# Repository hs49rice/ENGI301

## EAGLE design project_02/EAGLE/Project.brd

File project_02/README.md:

This directory contains all files for project 2 of ENGI301. The purpose of this project was to design a PCB board in EAGLE for the Clap-On LED Light Strip project.

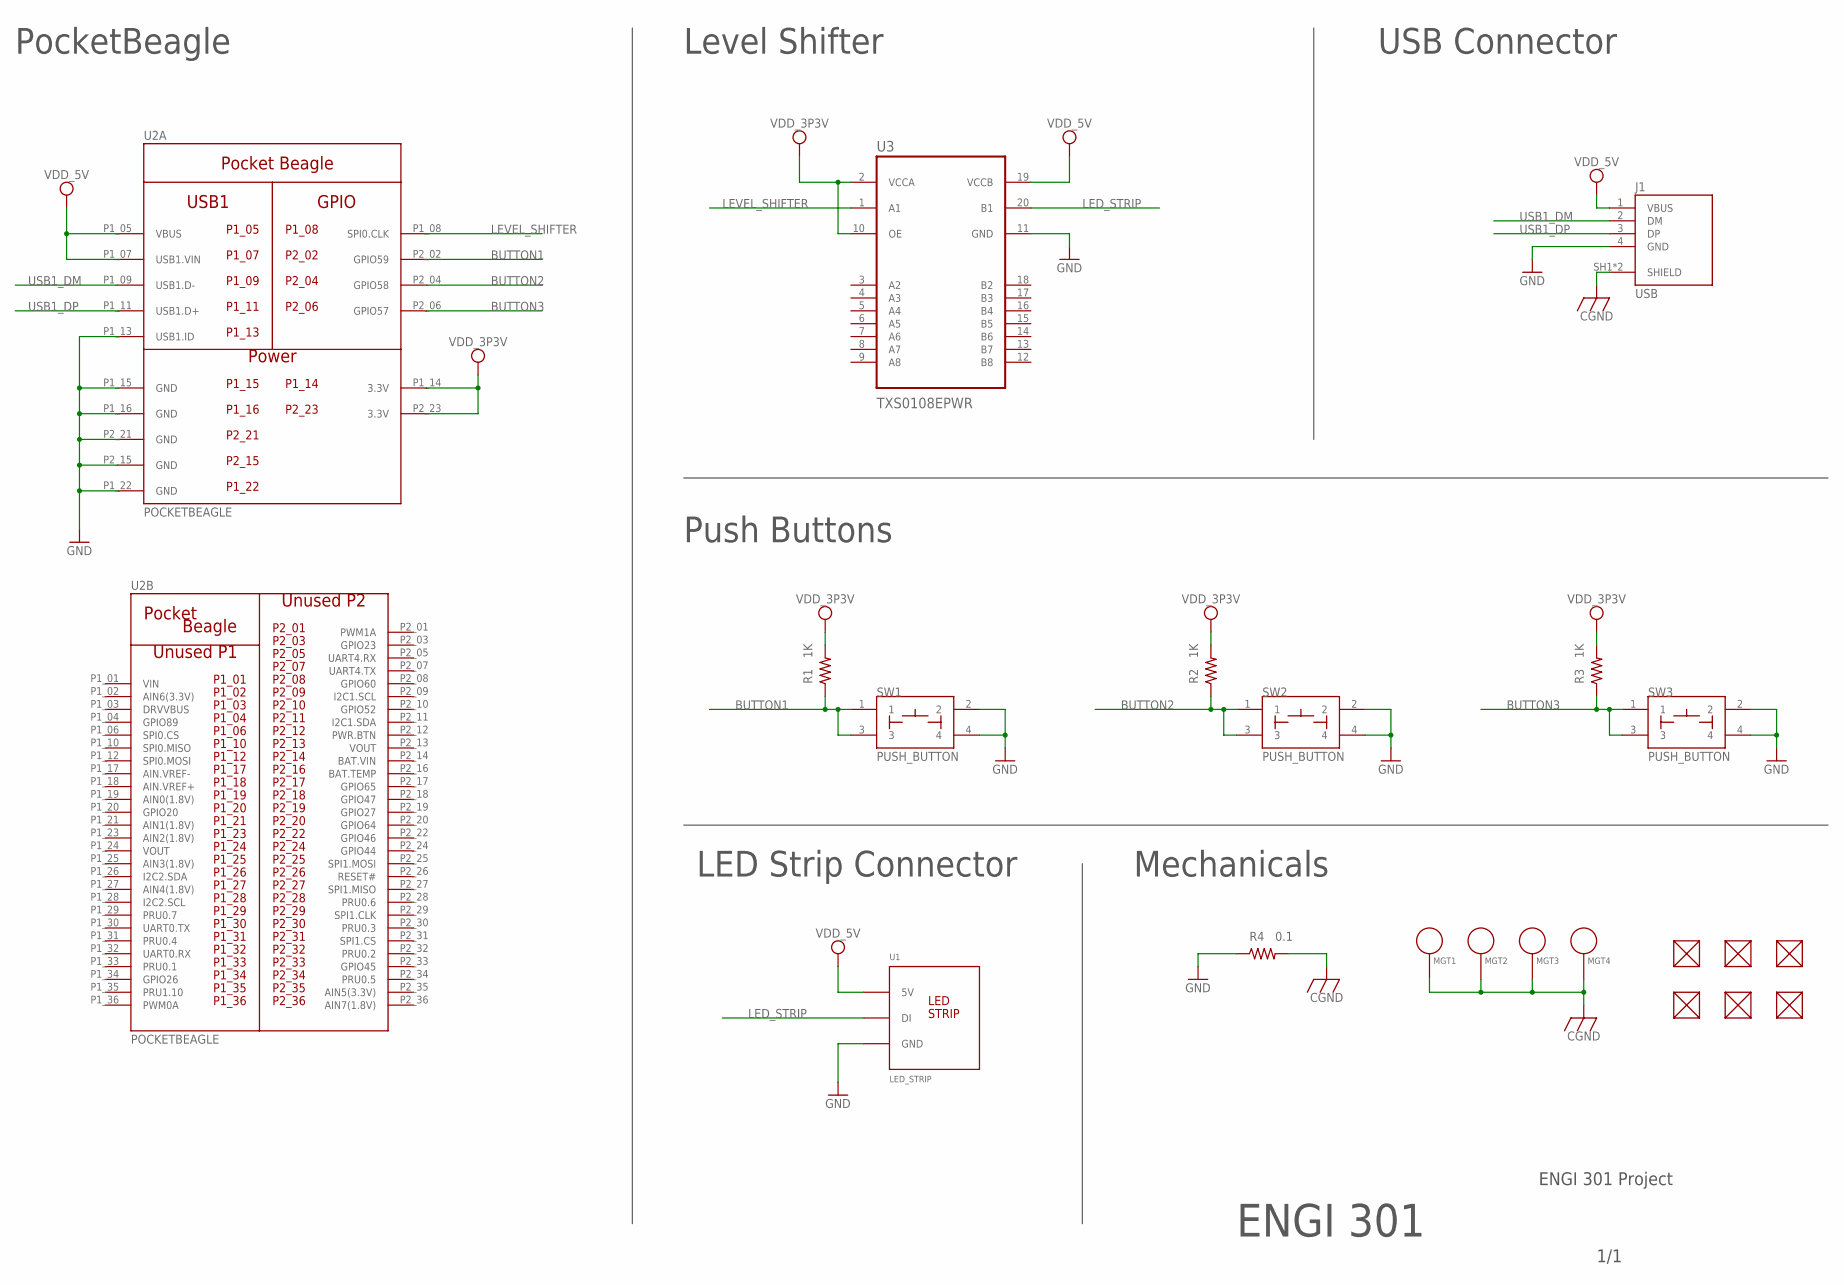
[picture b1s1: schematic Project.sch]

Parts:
FUD1, FUD2, FUD3, FUD4, FUD5, FUD6: FIDUCIAL; FIDUCIAL_40MIL
J1: USB
MGT1, MGT2, MGT3, MGT4: MOUNTING_HOLE
R1, R2, R3: 1K; R0603
R4: 0.1; R0805
SW1, SW2, SW3: PUSH_BUTTON; BUTTON_12.5MM
U1: LED_STRIP
U2: POCKETBEAGLE
U3: TXS0108EPWR; SOP65P640X120-20N

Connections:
BAT.VIN: U2.P2_14 (BAT.VIN)
BUTTON1: R1.1, SW1.1, SW1.3, U2.P2_02 (GPIO59)
BUTTON2: R2.1, SW2.1, SW2.3, U2.P2_04 (GPIO58)
BUTTON3: R3.1, SW3.1, SW3.3, U2.P2_06 (GPIO57)
CGND: J1.SH1 (SHIELD), J1.SH2 (SHIELD), MGT1.P$1, MGT2.P$1, MGT3.P$1, MGT4.P$1, R4.2
GND: J1.4 (GND), R4.1, SW1.2, SW1.4, SW2.2, SW2.4, SW3.2, SW3.4, U1.GND, U2.P1_13 (USB1.ID), U2.P1_15 (GND), U2.P1_16 (GND), U2.P1_22 (GND), U2.P2_15 (GND), U2.P2_21 (GND), U3.11 (GND)
LED_STRIP: U1.SIG (DI), U3.20 (B1)
LEVEL_SHIFTER: U2.P1_08 (SPI0.CLK), U3.1 (A1)
USB1_DM: J1.2 (DM), U2.P1_09 (USB1.D-)
USB1_DP: J1.3 (DP), U2.P1_11 (USB1.D+)
VDD_3P3V: R1.2, R2.2, R3.2, U2.P1_14 (3.3V), U2.P2_23 (3.3V), U3.2 (VCCA), U3.10 (OE)
VDD_5V: J1.1 (VBUS), U1.PWR (5V), U2.P1_05 (VBUS), U2.P1_07 (USB1.VIN), U3.19 (VCCB)
VIN: U2.P1_01 (VIN)
VOUT: U2.P1_24 (VOUT), U2.P2_13 (VOUT)

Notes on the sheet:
ENGI 301 Project
ENGI 301
1/1
PocketBeagle
Level Shifter
USB Connector
Push Buttons
LED Strip Connector
Mechanicals

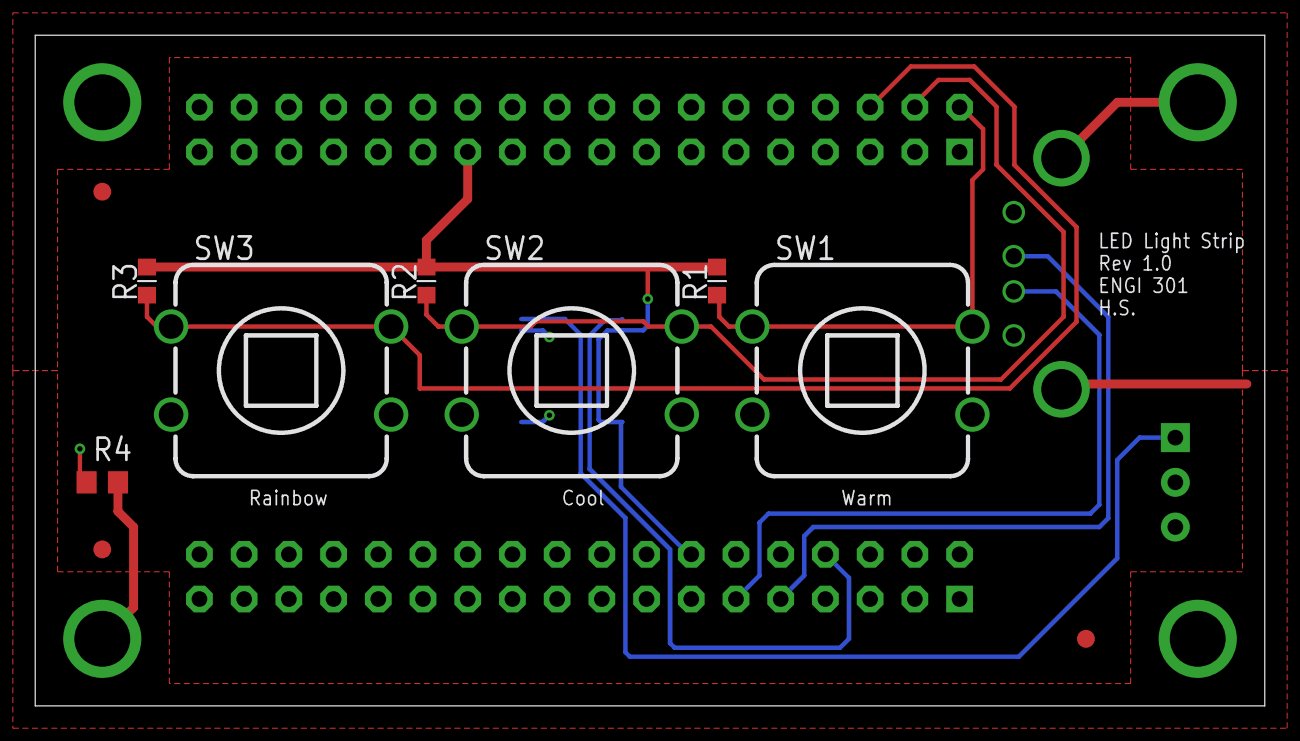
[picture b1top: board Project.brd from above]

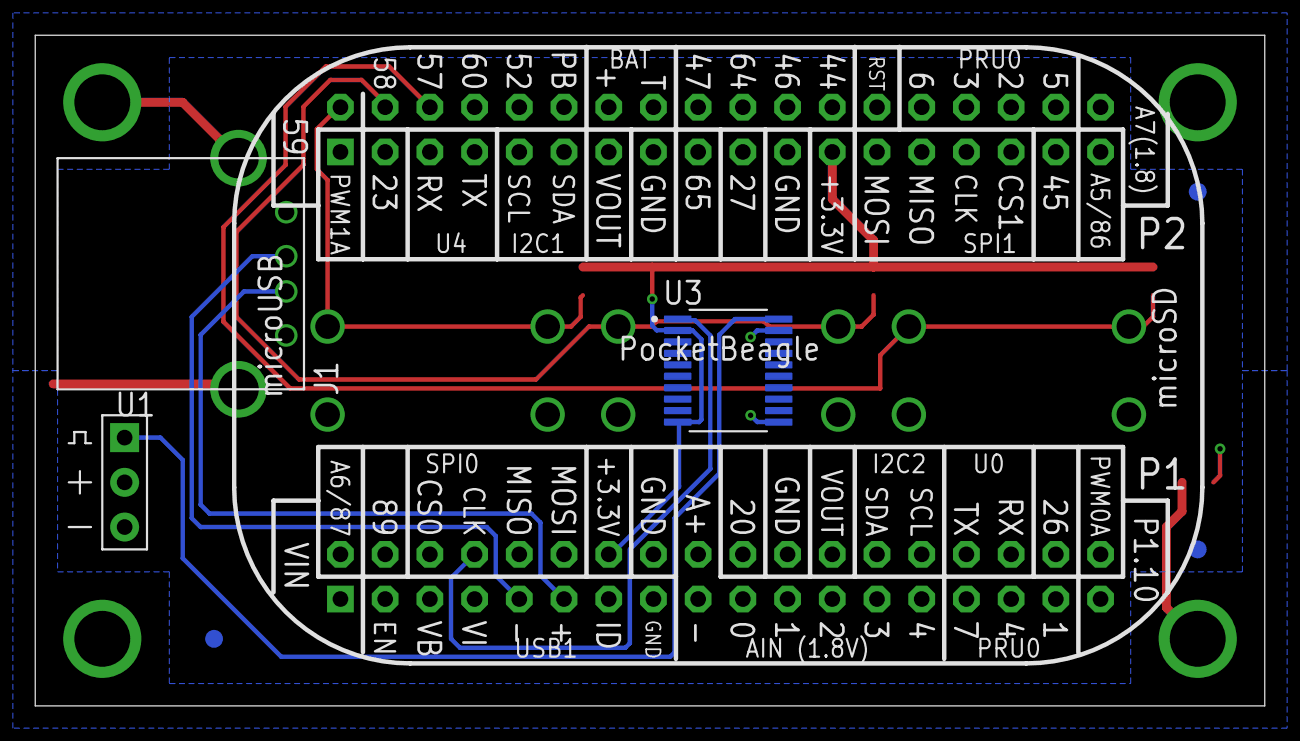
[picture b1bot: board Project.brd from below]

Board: 4 copper layers, 69.8 x 38.1 mm, 21 parts (7 on the bottom side), 12 nets.

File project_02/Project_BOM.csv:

"Qty";"Value";"Device";"Package";"Parts";"Description";"AVAILABILITY";"DESCRIPTION";"MF";"MP";"PACKAGE";"PRICE";"PURCHASE-URL";
"1";"0.1";"R_R0805";"R0805";"R4";"RESISTOR, American symbol";"";"";"";"";"";"";"";
"3";"1K";"R_R0603";"R0603";"R1, R2, R3";"RESISTOR, American symbol";"";"";"";"";"";"";"";
"6";"FIDUCIAL";"FIDUCIAL";"FIDUCIAL_40MIL";"FUD1, FUD2, FUD3, FUD4, FUD5, FUD6";"";"";"";"";"";"";"";"";
"1";"LED_STRIP";"LED_STRIP";"LED_STRIP";"U1";"";"";"";"";"";"";"";"";
"4";"MOUNTING_HOLE";"MOUNTING_HOLE";"MOUNTING_HOLE";"MGT1, MGT2, MGT3, MGT4";"Chassis Mounting Hole w/GND connection ability";"";"";"";"";"";"";"";
"1";"POCKETBEAGLE";"POCKETBEAGLE";"POCKETBEAGLE";"U2";"PocketBeagle";"";"";"";"";"";"";"";
"3";"PUSH_BUTTON";"PUSH_BUTTON";"BUTTON_12.5MM";"SW1, SW2, SW3";"";"";"";"";"";"";"";"";
"1";"TXS0108EPWR";"TXS0108EPWR";"SOP65P640X120-20N";"U3";"Check prices";"In Stock";" 8-bit bidirectional voltage-level shifter for open-drain and push-pull application 20-TSSOP -40 to 85 ";"Texas Instruments";"TXS0108EPWR";"TSSOP-20 Texas Instruments";"None";"https://pricing.snapeda.com/search/part/TXS0108EPWR/?ref=eda";
"1";"USB";"USB";"USB";"J1";"292303-1 USB Connector";"";"";"";"";"";"";"";

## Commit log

2021-10-05 Create simple_calc
2021-10-05 blink_led.py
2021-10-05 Rename simple_calc to simple_calc.py
2021-10-05 Rename blink_led to blink_led.py
2021-11-17 Create project_01
2021-11-17 Create text
2021-11-17 Create docs
2021-12-15 Create EAGLE
2021-12-15 Create temp
